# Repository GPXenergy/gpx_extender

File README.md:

# gpx_extender

The GPX Extender is a wireless link between the P1 port and the GPX Connector. It uses an STM32L011F4P6 and an off the shelf NRF24L01+ module to transparently transmit P1 port data. The device acts as transmitter when connected to the P1 port or as receiver when connected to the GPX Connector.

## firmware

Project files are included for Keil µVision >=v5.27.  

## hardware

The design files can be opened with Eagle v8.3.1 and up

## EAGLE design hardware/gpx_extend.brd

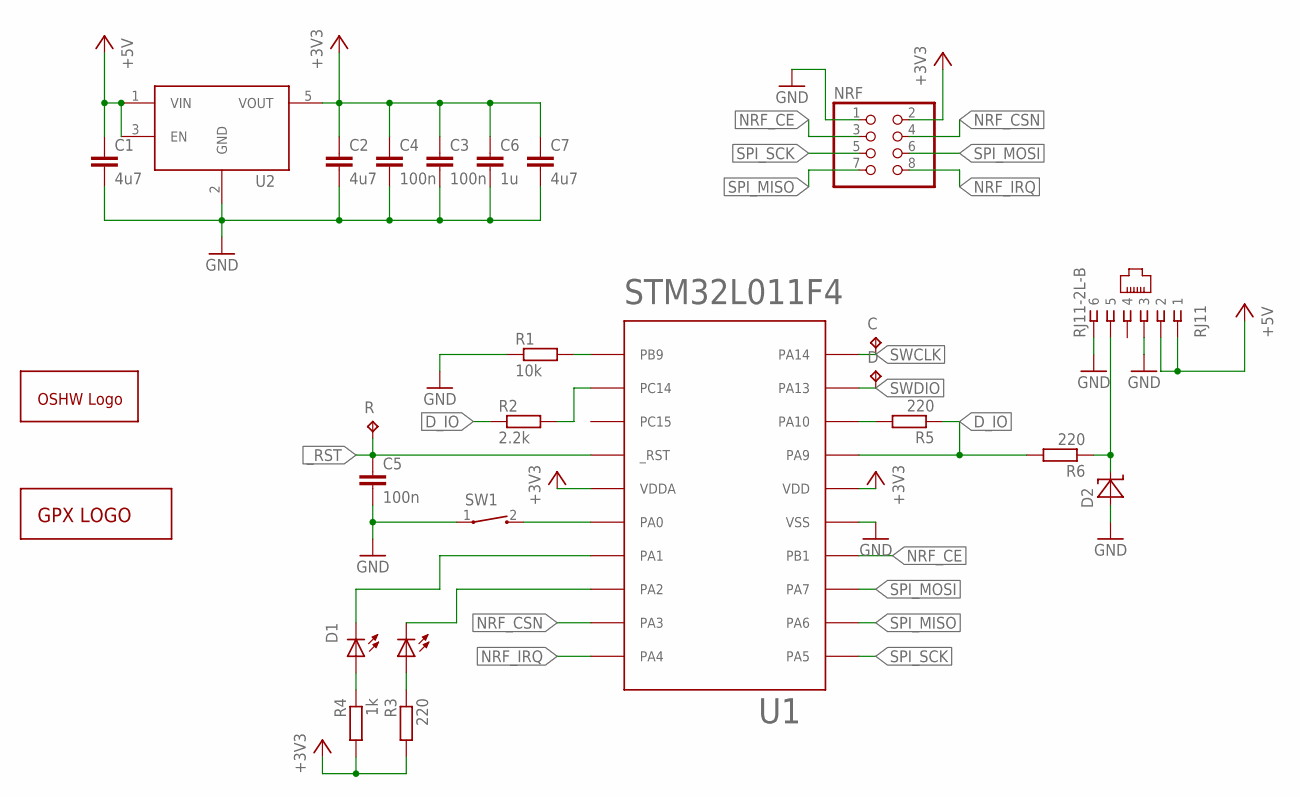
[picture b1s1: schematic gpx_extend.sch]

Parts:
C: TPTP10R; TP10R
C1, C2, C7: 4u7; 0603-MMGRID
C3, C4, C5: 100n; 0603-MMGRID
C6: 1u; 0603-MMGRID
D: TPTP10R; TP10R
D1: LED-DUAL; LED-1210
D2: UCLAMP3301HSOD523; SOD523
GOLD_ORB_SM1: OSHWLOGOLOGO5MM; OSHW_5MM
NRF: PINHD-2X4; 2X04
R: TPTP10R; TP10R
R1: 10k; 0603-MMGRID
R2: 2.2k; 0603-MMGRID
R3, R5, R6: 220; 0603-MMGRID
R4: 1k; 0603-MMGRID
RJ11: RJ11-2L-B; RJ11-NO_SHIELD
SW1: SW-SPST; TL3330
U1: STM32L011F4PX; TSSOP-20
U2: MIC550X; SOT23-5
U$1: GPX_LOGO

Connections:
+3V3: C2.1, C3.1, C4.1, C6.1, C7.1, NRF.2, R3.2, R4.2, U1.P$5 (VDDA), U1.P$16 (VDD), U2.5 (VOUT)
+5V: C1.1, RJ11.1, RJ11.2, U2.1 (VIN), U2.3 (EN)
BOOT0: R1.2, U1.P$1 (PB9)
BTN: SW1.2, U1.P$6 (PA0)
D_IO: R2.1, R5.1, R6.2, U1.P$17 (PA9)
GND: C1.2, C2.2, C3.2, C4.2, C5.2, C6.2, C7.2, D2.A, NRF.1, R1.1, RJ11.3, RJ11.6, SW1.1, U1.P$15 (VSS), U2.2 (GND)
unnamed: D2.C, R6.1, RJ11.5
unnamed: D1.1 (C0), U1.P$8 (PA2)
unnamed: D1.3 (C1), U1.P$7 (PA1)
unnamed: D1.2 (A0), R3.1
unnamed: D1.4 (A1), R4.1
NRF_CE: NRF.3, U1.P$14 (PB1)
NRF_CSN: NRF.4, U1.P$9 (PA3)
NRF_IRQ: NRF.8, U1.P$10 (PA4)
PC14: R2.2, U1.P$2 (PC14)
RX: R5.2, U1.P$18 (PA10)
SPI_MISO: NRF.7, U1.P$12 (PA6)
SPI_MOSI: NRF.6, U1.P$13 (PA7)
SPI_SCK: NRF.5, U1.P$11 (PA5)
SWCLK: C.TP, U1.P$20 (PA14)
SWDIO: D.TP, U1.P$19 (PA13)
_RST: C5.1, R.TP, U1.P$4 (_RST)

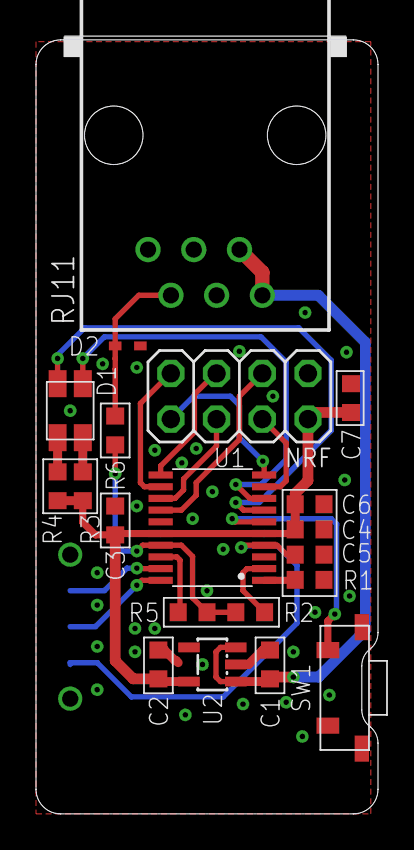
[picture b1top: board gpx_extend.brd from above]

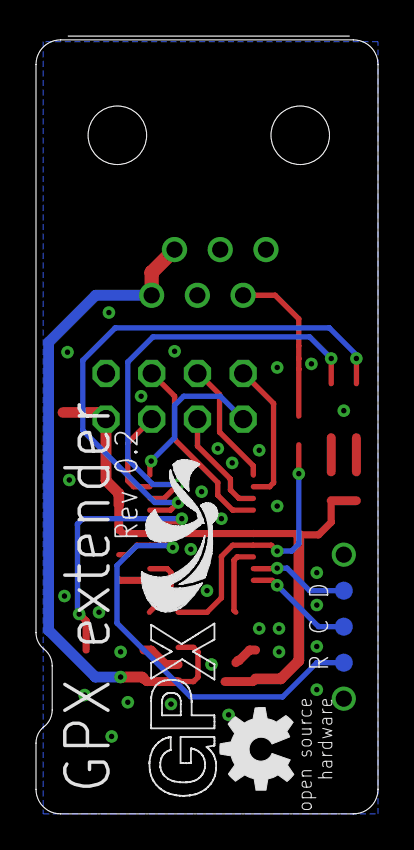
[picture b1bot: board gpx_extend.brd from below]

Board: 2 copper layers, 19.0 x 43.2 mm, 25 parts (5 on the bottom side), 22 nets.

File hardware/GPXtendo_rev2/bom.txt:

Part Value         Device        Package        Description
C1   4u7           C0603-S       0603           capacitor
C2   4u7           C0603-S       0603           capacitor
C3   100n          C0603-S       0603           capacitor
C4   100n          C0603-S       0603           capacitor
C5   100n          C0603-S       0603           capacitor
C6   1u            C0603-S       0603           capacitor
C7   4u7           C0603-S       0603           capacitor
D1   LED-DUAL      LED-DUAL      LED-1210       bi-color LED
NRF                PINHD-2X4     2X04           PIN HEADER
R1   10k           R0603-S       0603           resistor
R2   2.2k          R0603-S       0603           resistor
R3   220           R0603-S       0603           resistor
R4   220           R0603-S       0603           resistor
RJ11 RJ11-2L-B     RJ11-2L-B     RJ11           6-position RJ11 connector
SW1  SW-SPST       SW-SPST       TL3330         spst switch
U1   STM32L011F4PX STM32L011F4PX TSSOP-20       STM32 microcontroller
U2   AP7370-W5     AP7370-W5     SOT23-5        low-dropout voltage regulator

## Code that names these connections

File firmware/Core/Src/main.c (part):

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    
    Pin configuration:

    PA0     ------> BTN
    PA1     ------> LED1 (red)
    PA2     ------> LED2 (green)
    PA3     ------> CS
    PA4     ------> IRQ
    PA5     ------> SPI1_SCK
    PA6     ------> SPI1_MISO
    PA7     ------> SPI1_MOSI 
    PB1     ------> CE
    PA9     ------> UART2_TX, inverted, pullup enabled (if connected to gpxconn, else gpio input with pullup)
    PA10    ------> UART2_RX, OD, inverted (if connected to P1 port, else analog input)
    PA13    ------> SWDIO
    PA14    ------> SWCLK
    PC15    ------> driven high to function as strong pullup if connected to P1 port (2K ohms to UART2_RX)

    peripheral overview:
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
static connection_side detect_conn_side()
{
    // PA9      ------> USART2_TX
    // PA10     ------> USART2_RX
    
    // set both pins to input with pulldown on PA9
    GPIOA->PUPDR &= ~(GPIO_PUPDR_PUPD9 | GPIO_PUPDR_PUPD10);
    GPIOA->PUPDR |= GPIO_PUPDR_PUPD9_1;
    GPIOA->MODER &= ~(GPIO_MODER_MODE9 | GPIO_MODER_MODE10);
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{
    GPIO_InitTypeDef GPIO_InitStruct = {0};

    // unused pins: PC14, leave in reset state, portc clock disabled
    __HAL_RCC_GPIOA_CLK_ENABLE();
    __HAL_RCC_GPIOB_CLK_ENABLE();
    __HAL_RCC_GPIOC_CLK_ENABLE();
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    HAL_GPIO_Init(LED2_PORT, &GPIO_InitStruct);

    // button
    GPIO_InitStruct.Pin = BTN_PIN;
    GPIO_InitStruct.Mode = GPIO_MODE_IT_FALLING;
    GPIO_InitStruct.Pull = GPIO_PULLUP;
    GPIO_InitStruct.Speed = GPIO_SPEED_FREQ_LOW;
    HAL_GPIO_Init(BTN_PORT, &GPIO_InitStruct);
    
    
    // initial pin states
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
void EXTI0_1_IRQHandler(void)
{
    if(EXTI->PR & BTN_PIN){
        EXTI->PR |= BTN_PIN;
        if(!btn_timer_active){    // ignore if timer is already started, probably bounce
            start_btn_timer();
        }
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    if(LPTIM1->ISR & LPTIM_ISR_ARRM){
        LPTIM1->ICR |= LPTIM_ICR_ARRMCF;    // this timer has a seperate interrupt clear register
        
        if(gpio_read(BTN_PORT, BTN_PIN)){   // note button is pulldown so 0 = pressed
            released_time++;
        }
        else{
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
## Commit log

2021-03-11 add original keil and eagle projects
2021-03-11 add bom.txt
2021-03-11 add bill of materials
2021-03-11 add eagle project file
2021-05-26 rename and clean up project files
2021-05-26 update to latest version from local SVN
2021-05-26 add design files for rev2 board
2021-05-29 add license
2021-07-14 fix pin config for new hardware and reduce txpower for <100mA operation
2021-09-03 consolidate config into extender_config.h, add support for uart parity and stopbits
2021-11-05 fix DMA transfer bug at lower baudrates
